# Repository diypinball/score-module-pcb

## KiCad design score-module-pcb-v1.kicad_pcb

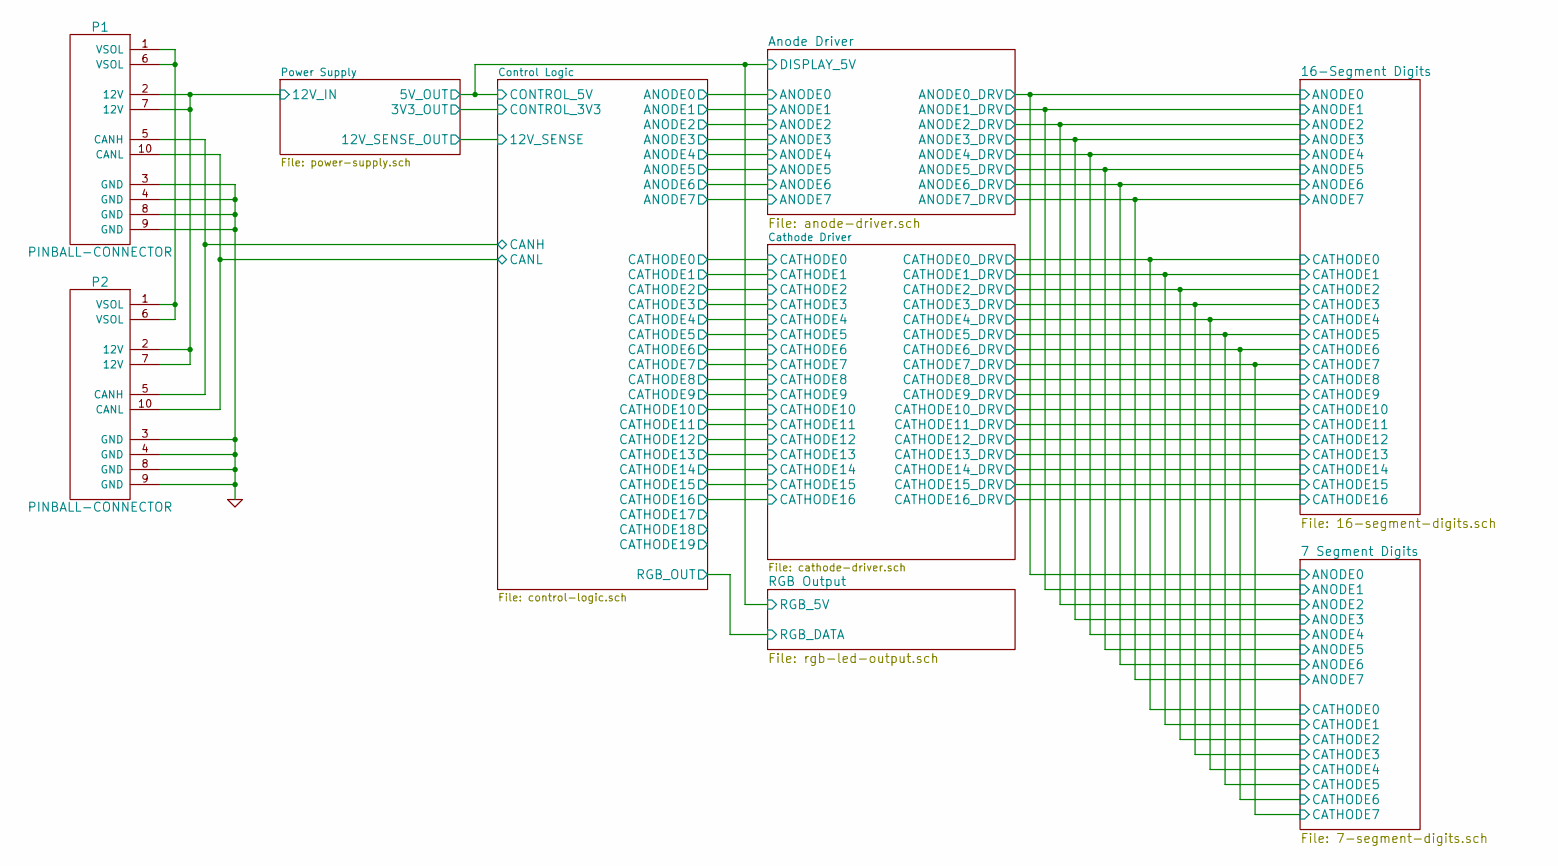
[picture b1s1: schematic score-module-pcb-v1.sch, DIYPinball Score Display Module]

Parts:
P1, P2: PINBALL-CONNECTOR; PINBALL-CONNECTOR-V

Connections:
/Control Logic/CANH: P1.5 (CANH), P2.5 (CANH); also elsewhere on the board
/Control Logic/CANL: P1.10 (CANL), P2.10 (CANL); also elsewhere on the board
/Power Supply/12V_IN: P1.2 (12V), P1.7 (12V), P2.2 (12V), P2.7 (12V); also elsewhere on the board
GND: P1.3 (GND), P1.4 (GND), P1.8 (GND), P1.9 (GND), P2.3 (GND), P2.4 (GND), P2.8 (GND), P2.9 (GND); also elsewhere on the board
unnamed: P1.1 (VSOL), P1.6 (VSOL), P2.1 (VSOL), P2.6 (VSOL)

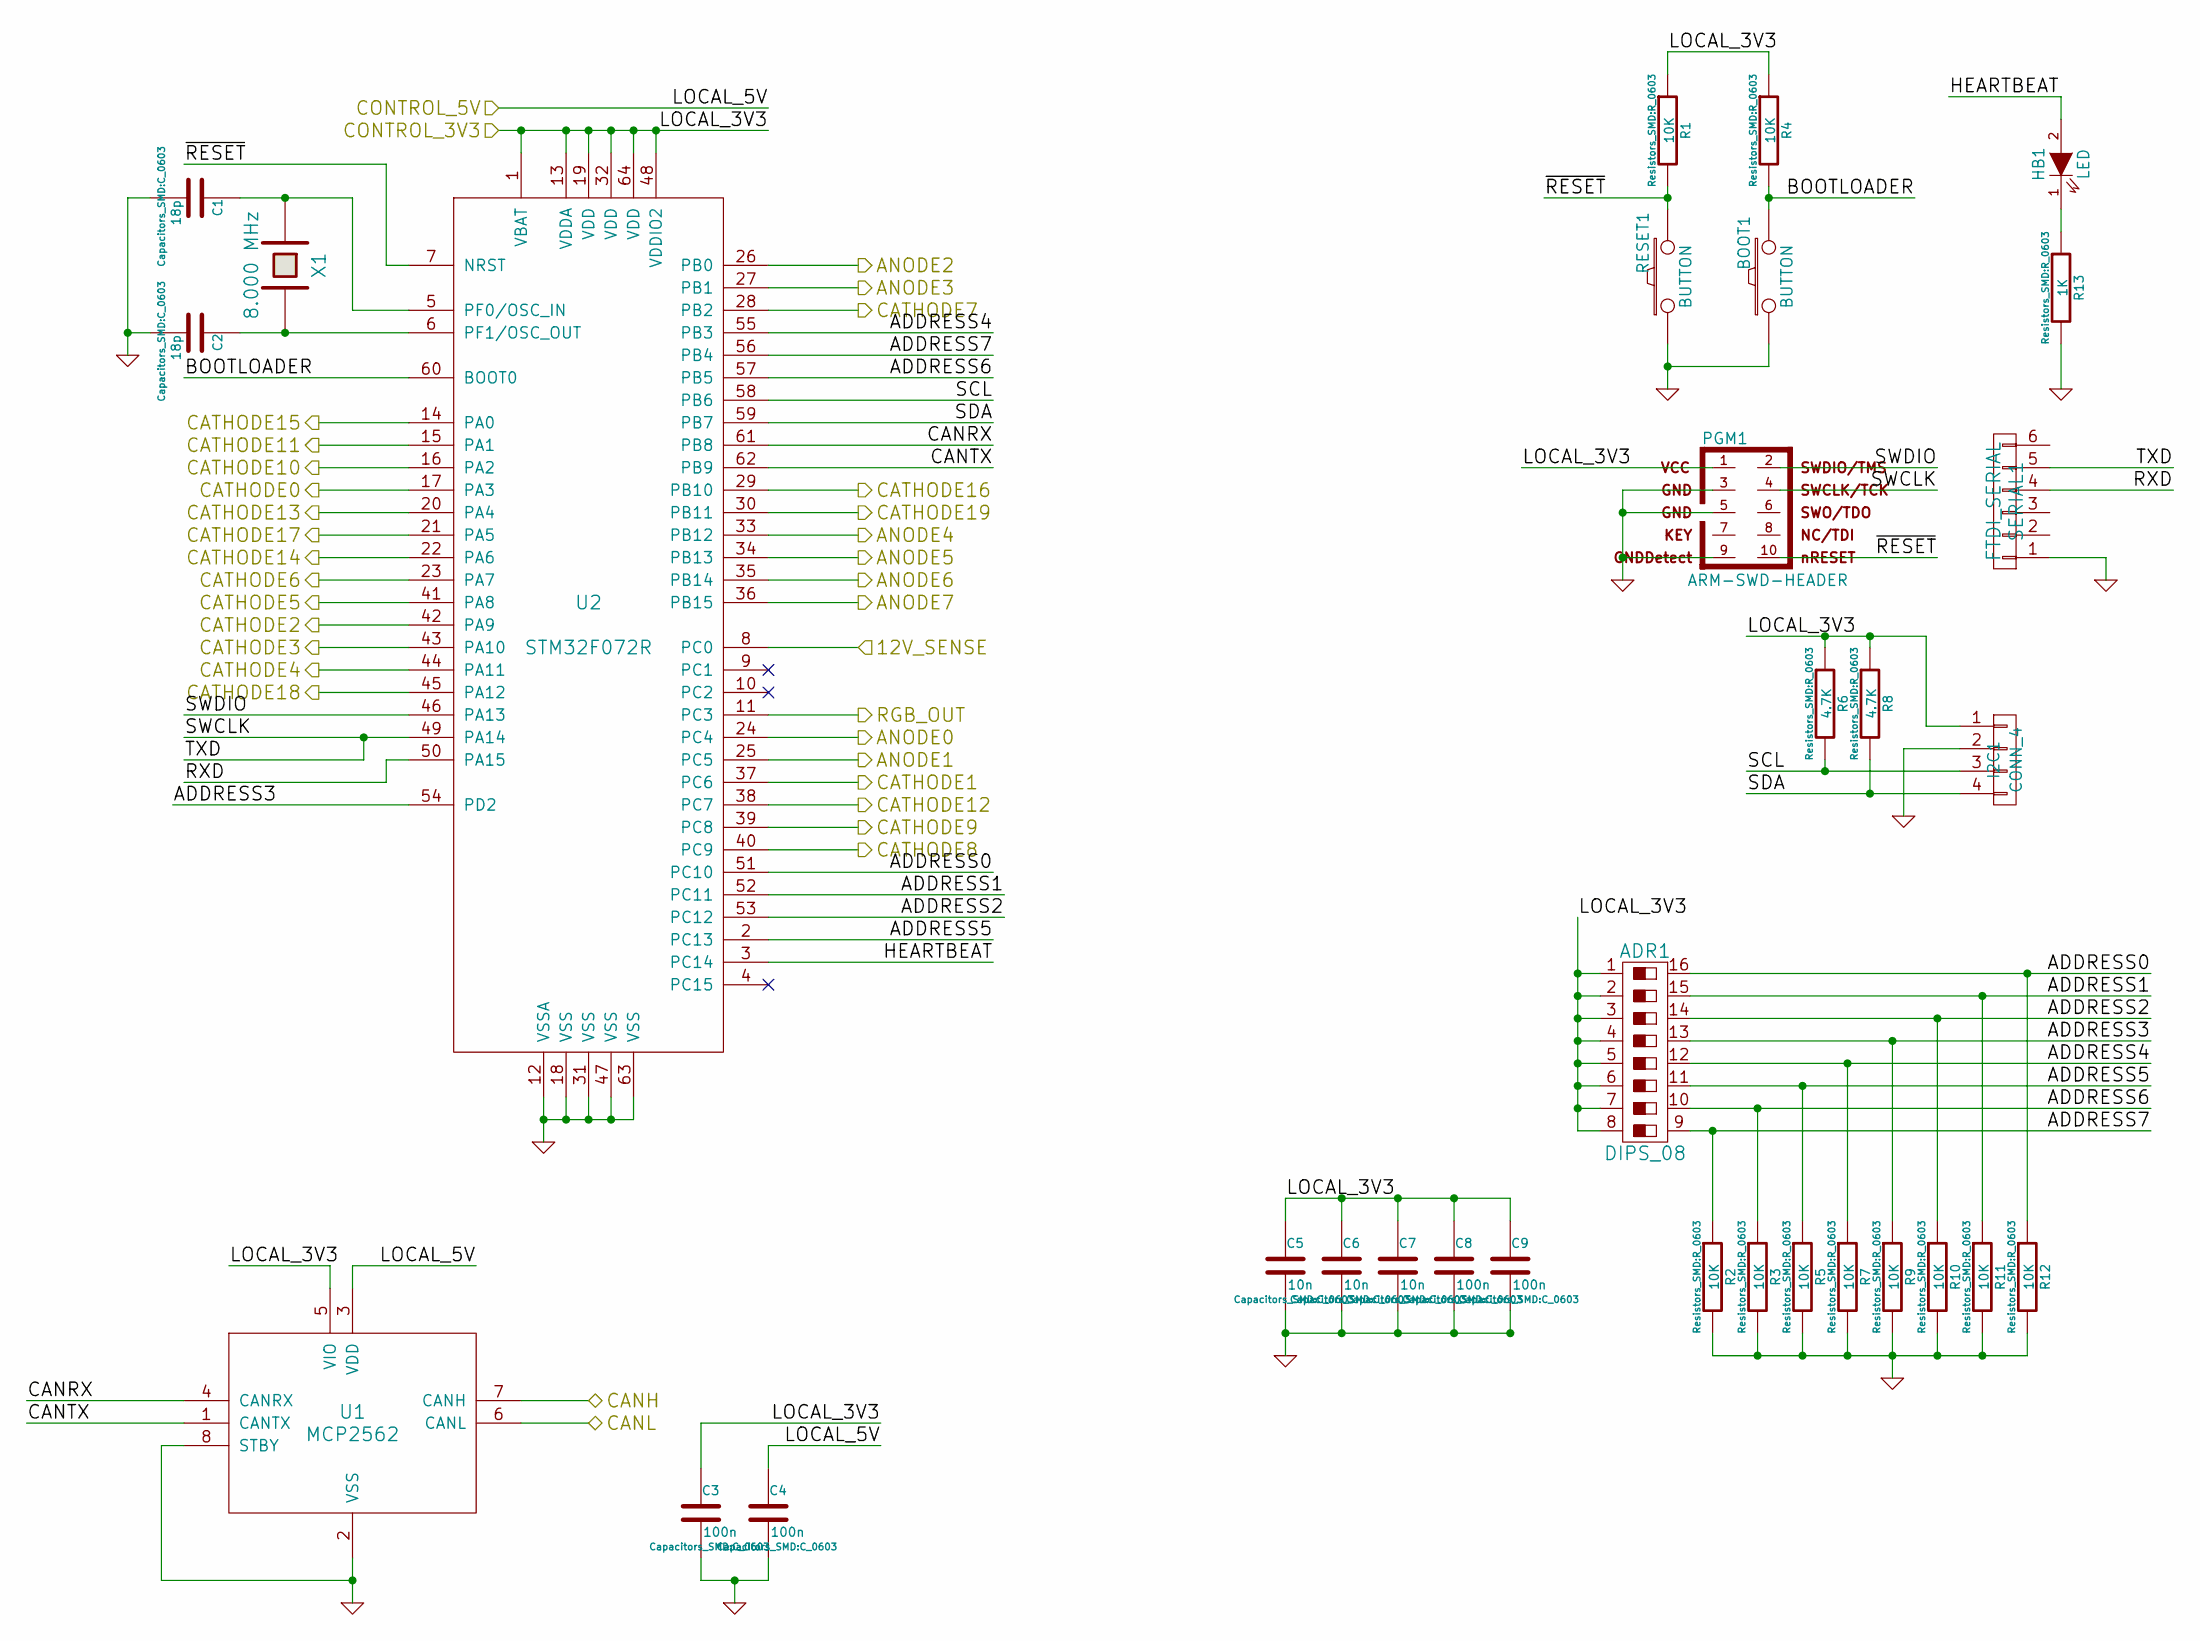
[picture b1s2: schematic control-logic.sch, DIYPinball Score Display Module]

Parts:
ADR1: DIPS_08; DIPSWITCH-SMT-08
BOOT1: BUTTON; SW_PUSH_SMALL
C1, C2: 18p; C_0603
C3, C4, C8, C9: 100n; C_0603
C5, C6, C7: 10n; C_0603
HB1: LED; LED-0603
I2C1: CONN_4; Socket_MOLEX-KK-RM2-54mm_Lock_4pin_straight
PGM1: ARM-SWD-HEADER; pin_array_5x2_50mil_smd
R1, R2, R3, R4, R5, R7, R9, R10, R11, R12: 10K; R_0603
R6, R8: 4.7K; R_0603
R13: 1K; R_0603
RESET1: BUTTON; SW_PUSH_SMALL
SERIAL1: FTDI_SERIAL; Socket_Strip_Straight_1x06
U1: MCP2562; SOIC-8_3.9x4.9mm_Pitch1.27mm
U2: STM32F072R; LQFP-64_10x10mm_Pitch0.5mm
X1: 8.000 MHz; Q_49U3HMS

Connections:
+3.3V: ADR1.1, ADR1.2, ADR1.3, ADR1.4, ADR1.5, ADR1.6, ADR1.7, ADR1.8, C3.1, C5.1, C6.1, C7.1, C8.1, C9.1, I2C1.1, PGM1.1, R1.1, R4.1, R6.1, R8.1, U1.5 (VIO), U2.1 (VBAT), U2.13 (VDDA), U2.19 (VDD), U2.32 (VDD), U2.48 (VDDIO2), U2.64 (VDD); also elsewhere on the board
+5V: C4.1, U1.3 (VDD); also elsewhere on the board
/Anode Driver/ANODE0: U2.24 (PC4); also elsewhere on the board
/Anode Driver/ANODE1: U2.25 (PC5); also elsewhere on the board
/Anode Driver/ANODE2: U2.26 (PB0); also elsewhere on the board
/Anode Driver/ANODE3: U2.27 (PB1); also elsewhere on the board
/Anode Driver/ANODE4: U2.33 (PB12); also elsewhere on the board
/Anode Driver/ANODE5: U2.34 (PB13); also elsewhere on the board
/Anode Driver/ANODE6: U2.35 (PB14); also elsewhere on the board
/Anode Driver/ANODE7: U2.36 (PB15); also elsewhere on the board
/Cathode Driver/CATHODE0: U2.17 (PA3); also elsewhere on the board
/Cathode Driver/CATHODE1: U2.37 (PC6); also elsewhere on the board
/Cathode Driver/CATHODE2: U2.42 (PA9); also elsewhere on the board
/Cathode Driver/CATHODE3: U2.43 (PA10); also elsewhere on the board
/Cathode Driver/CATHODE4: U2.44 (PA11); also elsewhere on the board
/Cathode Driver/CATHODE5: U2.41 (PA8); also elsewhere on the board
/Cathode Driver/CATHODE6: U2.23 (PA7); also elsewhere on the board
/Cathode Driver/CATHODE7: U2.28 (PB2); also elsewhere on the board
/Cathode Driver/CATHODE8: U2.40 (PC9); also elsewhere on the board
/Cathode Driver/CATHODE9: U2.39 (PC8); also elsewhere on the board
/Cathode Driver/CATHODE10: U2.16 (PA2); also elsewhere on the board
/Cathode Driver/CATHODE11: U2.15 (PA1); also elsewhere on the board
/Cathode Driver/CATHODE12: U2.38 (PC7); also elsewhere on the board
/Cathode Driver/CATHODE13: U2.20 (PA4); also elsewhere on the board
/Cathode Driver/CATHODE14: U2.22 (PA6); also elsewhere on the board
/Cathode Driver/CATHODE15: U2.14 (PA0); also elsewhere on the board
/Cathode Driver/CATHODE16: U2.29 (PB10); also elsewhere on the board
/Control Logic/12V_SENSE: U2.8 (PC0); also elsewhere on the board
/Control Logic/ADDRESS0: ADR1.16, R12.1, U2.51 (PC10)
/Control Logic/ADDRESS1: ADR1.15, R11.1, U2.52 (PC11)
/Control Logic/ADDRESS2: ADR1.14, R10.1, U2.53 (PC12)
/Control Logic/ADDRESS3: ADR1.13, R9.1, U2.54 (PD2)
/Control Logic/ADDRESS4: ADR1.12, R7.1, U2.55 (PB3)
/Control Logic/ADDRESS5: ADR1.11, R5.1, U2.2 (PC13)
/Control Logic/ADDRESS6: ADR1.10, R3.1, U2.57 (PB5)
/Control Logic/ADDRESS7: ADR1.9, R2.1, U2.56 (PB4)
/Control Logic/BOOTLOADER: BOOT1.2, R4.2, U2.60 (BOOT0)
/Control Logic/CANH: U1.7 (CANH); also elsewhere on the board
/Control Logic/CANL: U1.6 (CANL); also elsewhere on the board
/Control Logic/CANRX: U1.4 (CANRX), U2.61 (PB8)
/Control Logic/CANTX: U1.1 (CANTX), U2.62 (PB9)
/Control Logic/HEARTBEAT: HB1.2 (A), U2.3 (PC14)
/Control Logic/RXD: SERIAL1.4, U2.50 (PA15)
/Control Logic/SCL: I2C1.3, R6.2, U2.58 (PB6)
/Control Logic/SDA: I2C1.4, R8.2, U2.59 (PB7)
/Control Logic/SWCLK: PGM1.4, SERIAL1.5, U2.49 (PA14)
/Control Logic/SWDIO: PGM1.2, U2.46 (PA13)
/Control Logic/~RESET: PGM1.10, R1.2, RESET1.2, U2.7 (NRST)
/RGB Output/RGB_DATA: U2.11 (PC3); also elsewhere on the board
GND: BOOT1.1, C1.2, C2.2, C3.2, C4.2, C5.2, C6.2, C7.2, C8.2, C9.2, I2C1.2, PGM1.3, PGM1.5, PGM1.9, R2.2, R3.2, R5.2, R7.2, R9.2, R10.2, R11.2, R12.2, R13.2, RESET1.1, SERIAL1.1, U1.2 (VSS), U1.8 (STBY), U2.12 (VSSA), U2.18 (VSS), U2.31 (VSS), U2.47 (VSS), U2.63 (VSS); also elsewhere on the board
unnamed: C1.1, U2.5 (PF0/OSC_IN), X1.1
unnamed: C2.1, U2.6 (PF1/OSC_OUT), X1.2
unnamed: HB1.1 (K), R13.1

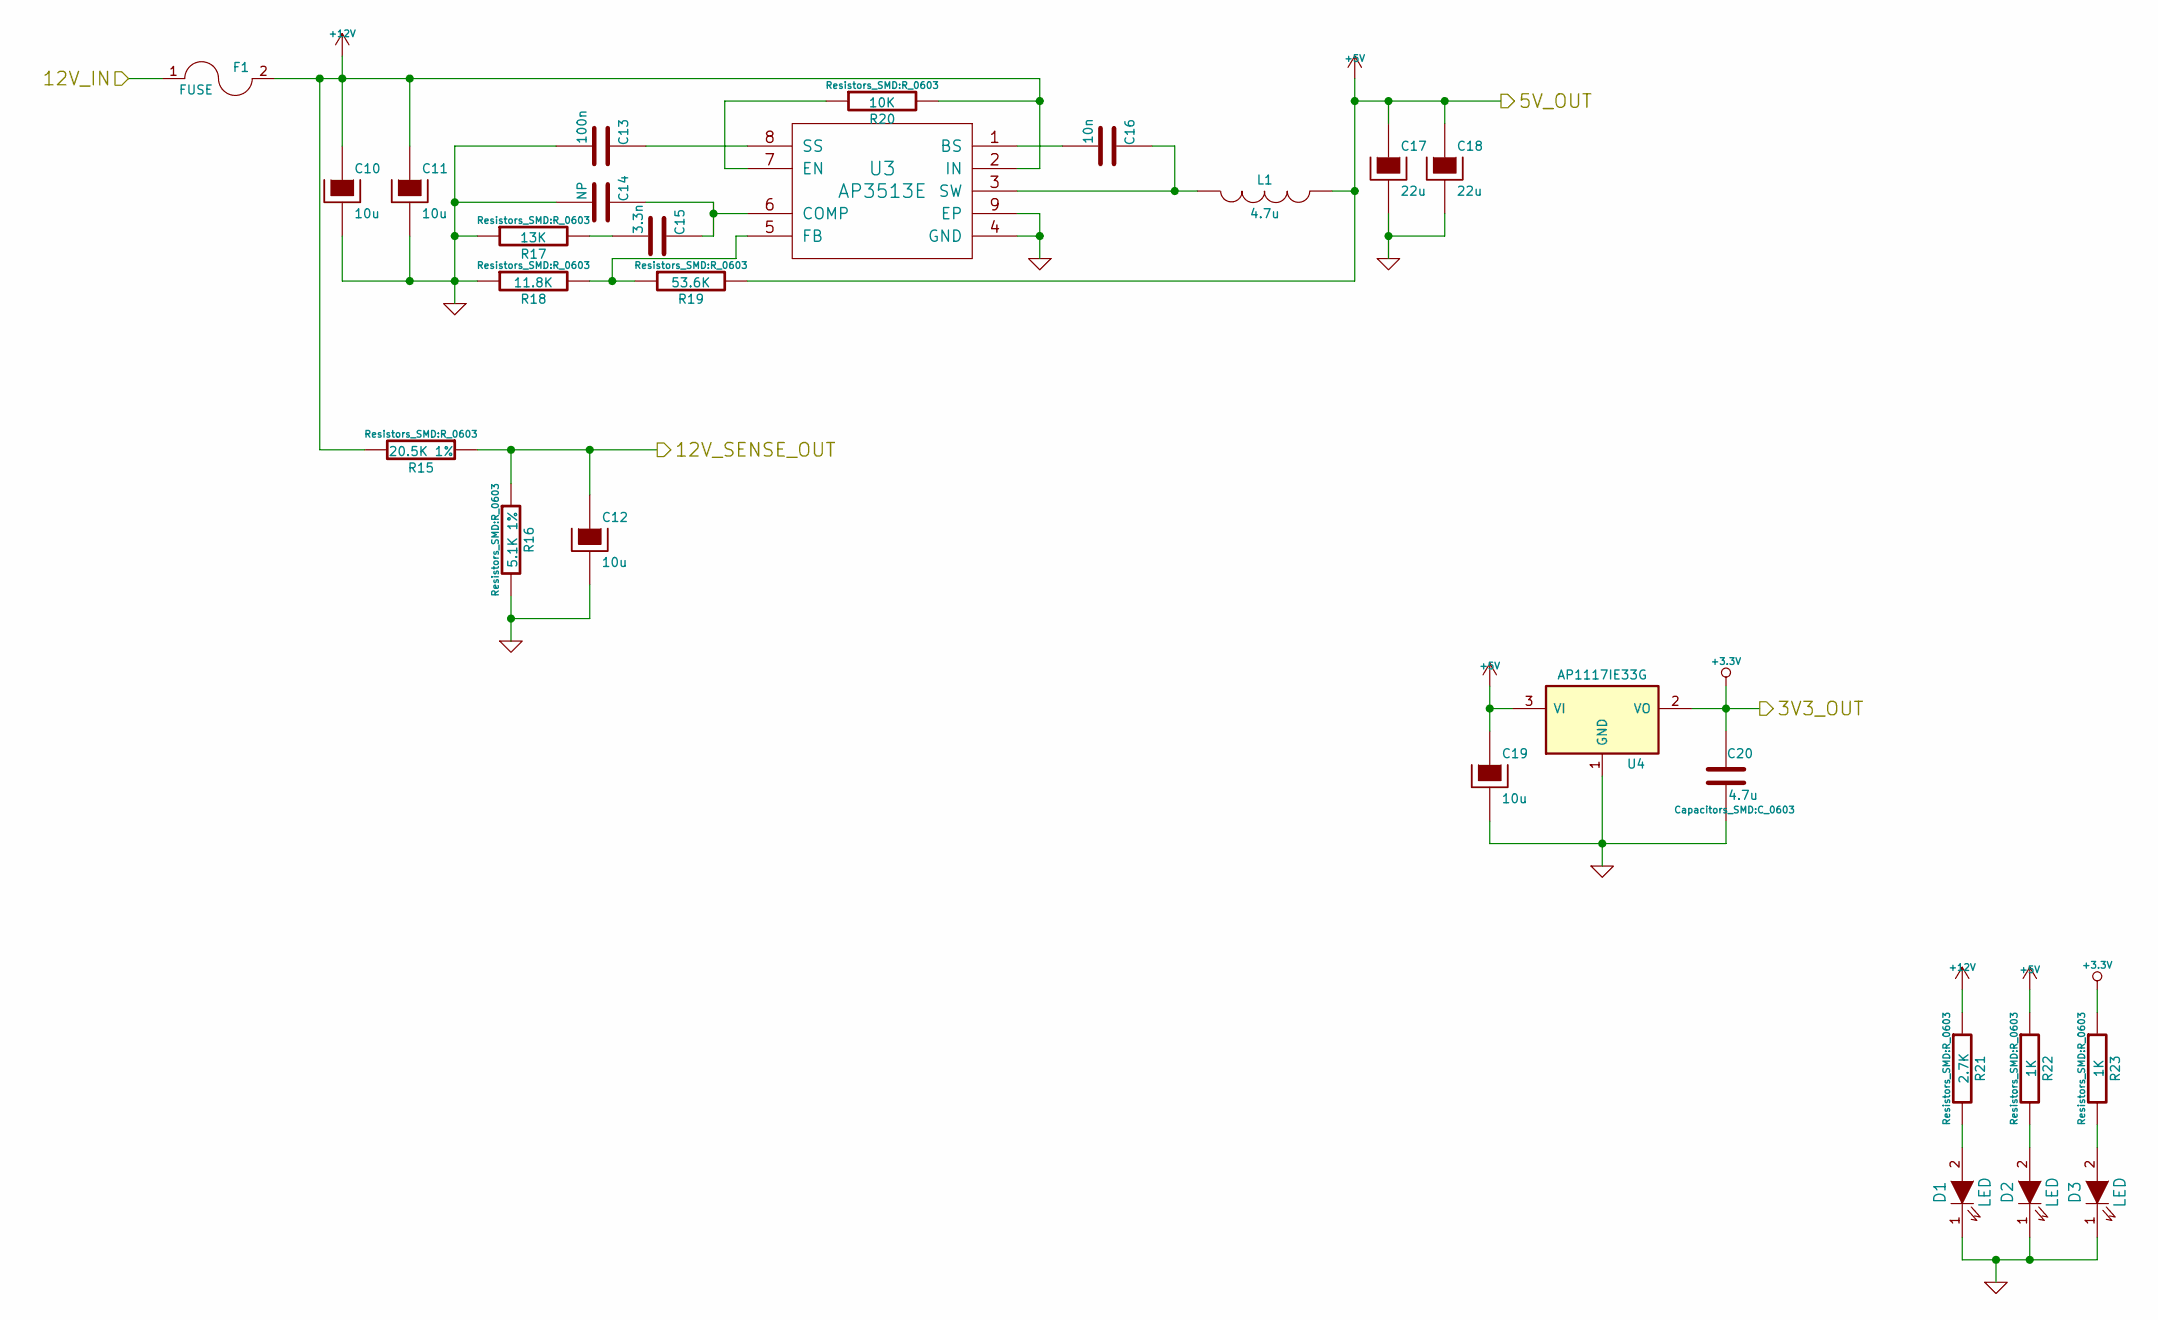
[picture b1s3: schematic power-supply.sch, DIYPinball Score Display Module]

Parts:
C10, C11: 10u; c_elec_5x5.8
C12, C19: 10u; C_0805
C13: 100n; C_0603
C14: NP; C_0603
C15: 3.3n; C_0603
C16: 10n; C_0603
C17, C18: 22u; c_elec_5x5.8
C20: 4.7u; C_0603
D1, D2, D3: LED; LED-0603
F1: FUSE; FC203-20MM
L1: 4.7u; SELF-WE-PD3S
R15: 20.5K 1%; R_0603
R16: 5.1K 1%; R_0603
R17: 13K; R_0603
R18: 11.8K; R_0603
R19: 53.6K; R_0603
R20: 10K; R_0603
R21: 2.7K; R_0603
R22, R23: 1K; R_0603
U3: AP3513E; SOIC-8-1EP_3.9x4.9mm_Pitch1.27mm
U4: AP1117IE33G; SOT-223

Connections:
+3.3V: C20.1, R23.1, U4.2 (VO); also elsewhere on the board
+5V: C17.1, C18.1, C19.1, L1.2, R19.2, R22.1, U4.3 (VI); also elsewhere on the board
+12V: C10.1, C11.1, F1.2, R15.2, R20.2, R21.1, U3.2 (IN)
/Control Logic/12V_SENSE: C12.1, R15.1, R16.1; also elsewhere on the board
/Power Supply/12V_IN: F1.1; also elsewhere on the board
GND: C10.2, C11.2, C12.2, C13.2, C14.2, C17.2, C18.2, C19.2, C20.2, D1.1 (K), D2.1 (K), D3.1 (K), R16.2, R17.1, R18.1, U3.4 (GND), U3.9 (EP), U4.1 (GND); also elsewhere on the board
unnamed: C13.1, U3.8 (SS)
unnamed: C14.1, C15.1, U3.6 (COMP)
unnamed: C15.2, R17.2
unnamed: C16.1, L1.1, U3.3 (SW)
unnamed: C16.2, U3.1 (BS)
unnamed: D1.2 (A), R21.2
unnamed: D2.2 (A), R22.2
unnamed: D3.2 (A), R23.2
unnamed: R18.2, R19.1, U3.5 (FB)
unnamed: R20.1, U3.7 (EN)

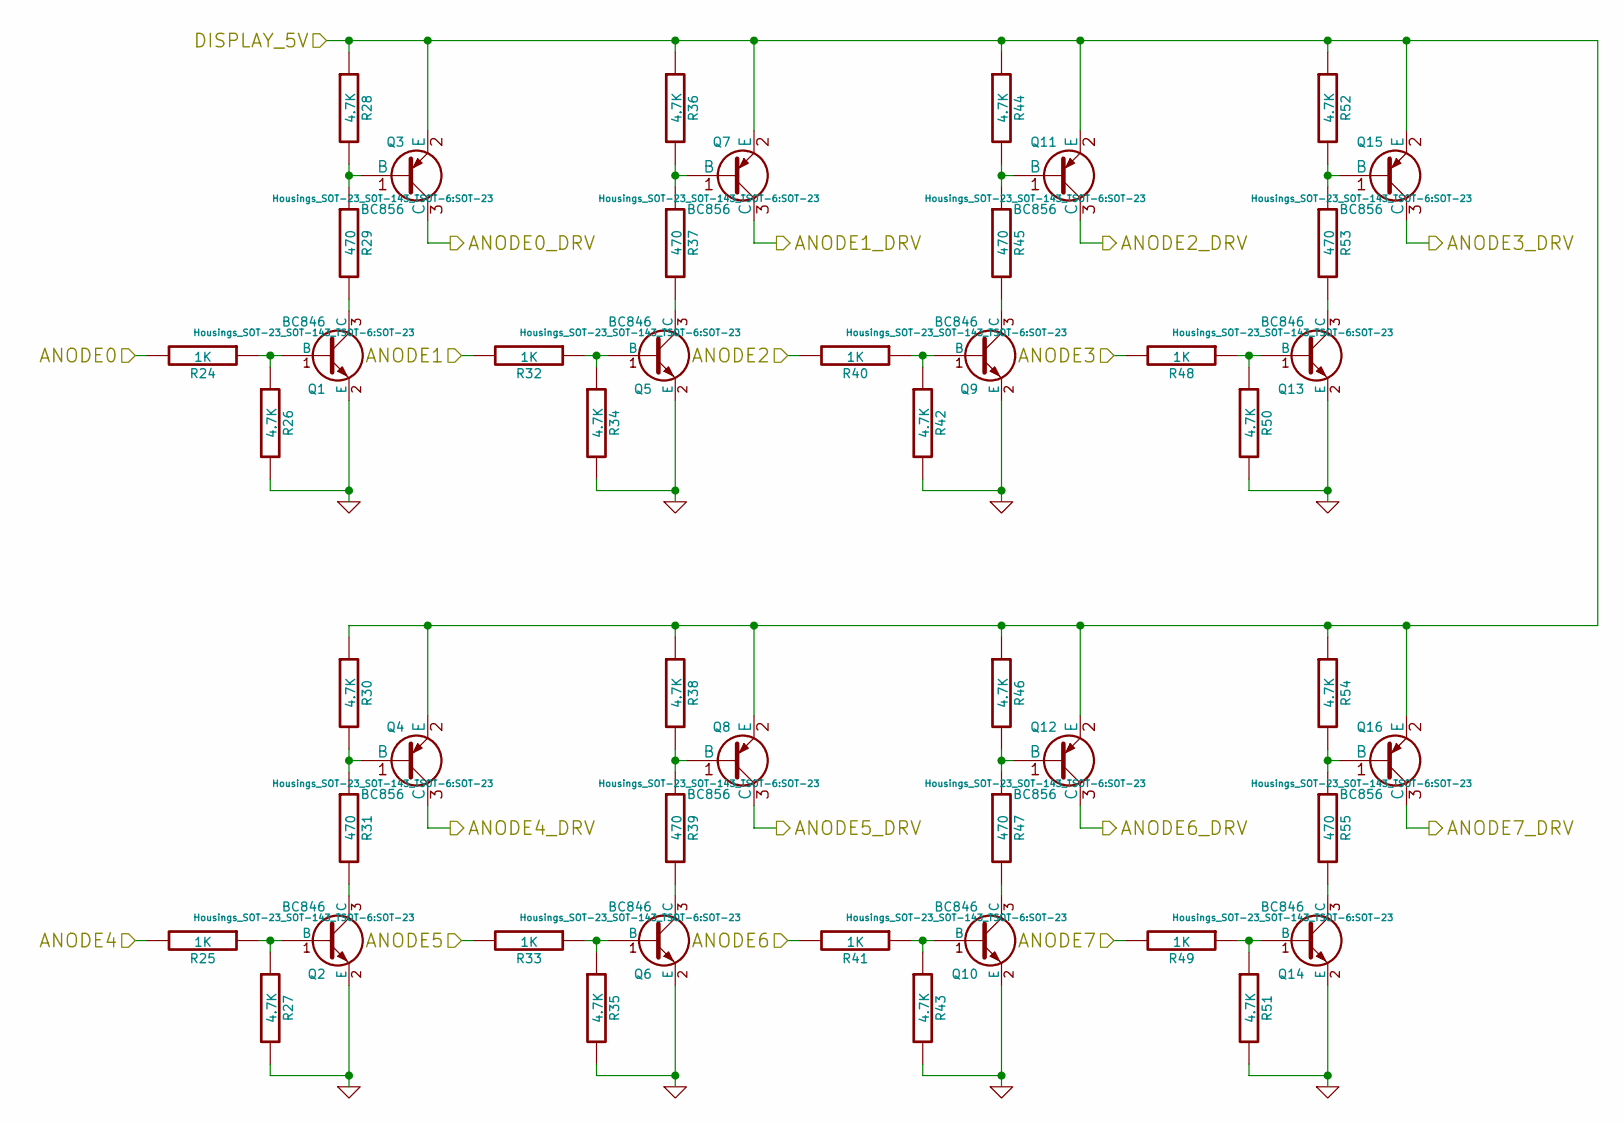
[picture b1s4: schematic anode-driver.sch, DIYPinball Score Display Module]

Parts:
Q1, Q2, Q5, Q6, Q9, Q10, Q13, Q14: BC846; SOT-23
Q3, Q4, Q7, Q8, Q11, Q12, Q15, Q16: BC856; SOT-23
R24, R25, R32, R33, R40, R41, R48, R49: 1K; R_0603
R26, R27, R28, R30, R34, R35, R36, R38, R42, R43, R44, R46, R50, R51, R52, R54: 4.7K; R_0603
R29, R31, R37, R39, R45, R47, R53, R55: 470; R_0603

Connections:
+5V: Q3.2 (E), Q4.2 (E), Q7.2 (E), Q8.2 (E), Q11.2 (E), Q12.2 (E), Q15.2 (E), Q16.2 (E), R28.1, R30.1, R36.1, R38.1, R44.1, R46.1, R52.1, R54.1; also elsewhere on the board
/16-Segment Digits/ANODE0: Q3.3 (C); also elsewhere on the board
/16-Segment Digits/ANODE1: Q7.3 (C); also elsewhere on the board
/16-Segment Digits/ANODE2: Q11.3 (C); also elsewhere on the board
/16-Segment Digits/ANODE3: Q15.3 (C); also elsewhere on the board
/16-Segment Digits/ANODE4: Q4.3 (C); also elsewhere on the board
/16-Segment Digits/ANODE5: Q8.3 (C); also elsewhere on the board
/16-Segment Digits/ANODE6: Q12.3 (C); also elsewhere on the board
/16-Segment Digits/ANODE7: Q16.3 (C); also elsewhere on the board
/Anode Driver/ANODE0: R24.2; also elsewhere on the board
/Anode Driver/ANODE1: R32.2; also elsewhere on the board
/Anode Driver/ANODE2: R40.2; also elsewhere on the board
/Anode Driver/ANODE3: R48.2; also elsewhere on the board
/Anode Driver/ANODE4: R25.2; also elsewhere on the board
/Anode Driver/ANODE5: R33.2; also elsewhere on the board
/Anode Driver/ANODE6: R41.2; also elsewhere on the board
/Anode Driver/ANODE7: R49.2; also elsewhere on the board
GND: Q1.2 (E), Q2.2 (E), Q5.2 (E), Q6.2 (E), Q9.2 (E), Q10.2 (E), Q13.2 (E), Q14.2 (E), R26.2, R27.2, R34.2, R35.2, R42.2, R43.2, R50.2, R51.2; also elsewhere on the board
unnamed: Q1.1 (B), R24.1, R26.1
unnamed: Q1.3 (C), R29.2
unnamed: Q2.1 (B), R25.1, R27.1
unnamed: Q2.3 (C), R31.2
unnamed: Q3.1 (B), R28.2, R29.1
unnamed: Q4.1 (B), R30.2, R31.1
unnamed: Q5.1 (B), R32.1, R34.1
unnamed: Q5.3 (C), R37.2
unnamed: Q6.1 (B), R33.1, R35.1
unnamed: Q6.3 (C), R39.2
unnamed: Q7.1 (B), R36.2, R37.1
unnamed: Q8.1 (B), R38.2, R39.1
unnamed: Q9.1 (B), R40.1, R42.1
unnamed: Q9.3 (C), R45.2
unnamed: Q10.1 (B), R41.1, R43.1
unnamed: Q10.3 (C), R47.2
unnamed: Q11.1 (B), R44.2, R45.1
unnamed: Q12.1 (B), R46.2, R47.1
unnamed: Q13.1 (B), R48.1, R50.1
unnamed: Q13.3 (C), R53.2
unnamed: Q14.1 (B), R49.1, R51.1
unnamed: Q14.3 (C), R55.2
unnamed: Q15.1 (B), R52.2, R53.1
unnamed: Q16.1 (B), R54.2, R55.1

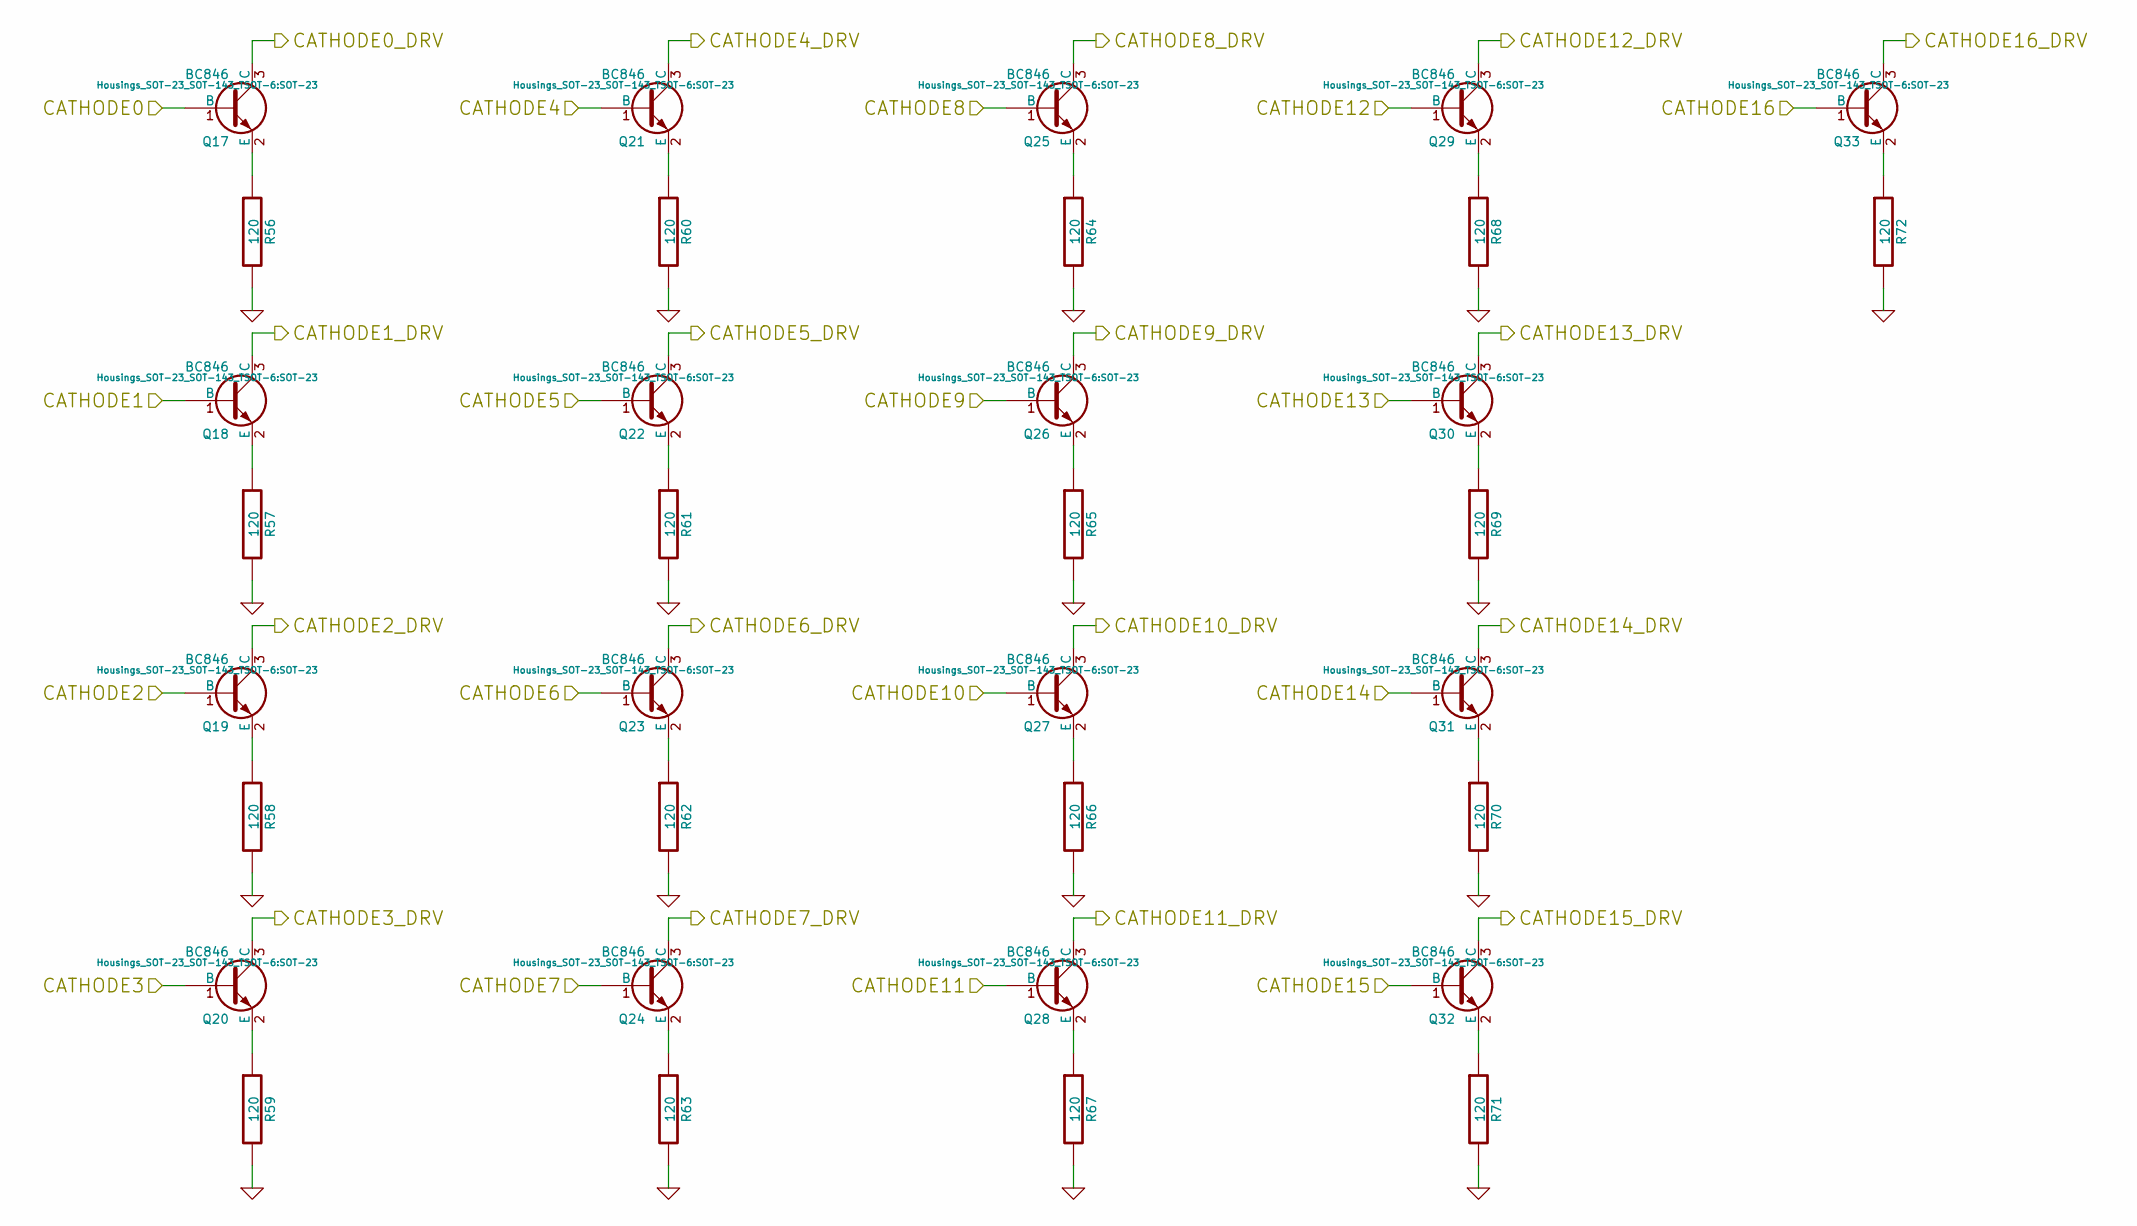
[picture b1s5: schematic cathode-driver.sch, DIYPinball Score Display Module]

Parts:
Q17, Q18, Q19, Q20, Q21, Q22, Q23, Q24, Q25, Q26, Q27, Q28, Q29, Q30, Q31, Q32, Q33: BC846; SOT-23
R56, R57, R58, R59, R60, R61, R62, R63, R64, R65, R66, R67, R68, R69, R70, R71, R72: 120; R_0603

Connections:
/16-Segment Digits/CATHODE0: Q17.3 (C); also elsewhere on the board
/16-Segment Digits/CATHODE1: Q18.3 (C); also elsewhere on the board
/16-Segment Digits/CATHODE2: Q19.3 (C); also elsewhere on the board
/16-Segment Digits/CATHODE3: Q20.3 (C); also elsewhere on the board
/16-Segment Digits/CATHODE4: Q21.3 (C); also elsewhere on the board
/16-Segment Digits/CATHODE5: Q22.3 (C); also elsewhere on the board
/16-Segment Digits/CATHODE6: Q23.3 (C); also elsewhere on the board
/16-Segment Digits/CATHODE7: Q24.3 (C); also elsewhere on the board
/16-Segment Digits/CATHODE8: Q25.3 (C); also elsewhere on the board
/16-Segment Digits/CATHODE9: Q26.3 (C); also elsewhere on the board
/16-Segment Digits/CATHODE10: Q27.3 (C); also elsewhere on the board
/16-Segment Digits/CATHODE11: Q28.3 (C); also elsewhere on the board
/16-Segment Digits/CATHODE12: Q29.3 (C); also elsewhere on the board
/16-Segment Digits/CATHODE13: Q30.3 (C); also elsewhere on the board
/16-Segment Digits/CATHODE14: Q31.3 (C); also elsewhere on the board
/16-Segment Digits/CATHODE15: Q32.3 (C); also elsewhere on the board
/16-Segment Digits/CATHODE16: Q33.3 (C); also elsewhere on the board
/Cathode Driver/CATHODE0: Q17.1 (B); also elsewhere on the board
/Cathode Driver/CATHODE1: Q18.1 (B); also elsewhere on the board
/Cathode Driver/CATHODE2: Q19.1 (B); also elsewhere on the board
/Cathode Driver/CATHODE3: Q20.1 (B); also elsewhere on the board
/Cathode Driver/CATHODE4: Q21.1 (B); also elsewhere on the board
/Cathode Driver/CATHODE5: Q22.1 (B); also elsewhere on the board
/Cathode Driver/CATHODE6: Q23.1 (B); also elsewhere on the board
/Cathode Driver/CATHODE7: Q24.1 (B); also elsewhere on the board
/Cathode Driver/CATHODE8: Q25.1 (B); also elsewhere on the board
/Cathode Driver/CATHODE9: Q26.1 (B); also elsewhere on the board
/Cathode Driver/CATHODE10: Q27.1 (B); also elsewhere on the board
/Cathode Driver/CATHODE11: Q28.1 (B); also elsewhere on the board
/Cathode Driver/CATHODE12: Q29.1 (B); also elsewhere on the board
/Cathode Driver/CATHODE13: Q30.1 (B); also elsewhere on the board
/Cathode Driver/CATHODE14: Q31.1 (B); also elsewhere on the board
/Cathode Driver/CATHODE15: Q32.1 (B); also elsewhere on the board
/Cathode Driver/CATHODE16: Q33.1 (B); also elsewhere on the board
GND: R56.2, R57.2, R58.2, R59.2, R60.2, R61.2, R62.2, R63.2, R64.2, R65.2, R66.2, R67.2, R68.2, R69.2, R70.2, R71.2, R72.2; also elsewhere on the board
unnamed: Q17.2 (E), R56.1
unnamed: Q18.2 (E), R57.1
unnamed: Q19.2 (E), R58.1
unnamed: Q20.2 (E), R59.1
unnamed: Q21.2 (E), R60.1
unnamed: Q22.2 (E), R61.1
unnamed: Q23.2 (E), R62.1
unnamed: Q24.2 (E), R63.1
unnamed: Q25.2 (E), R64.1
unnamed: Q26.2 (E), R65.1
unnamed: Q27.2 (E), R66.1
unnamed: Q28.2 (E), R67.1
unnamed: Q29.2 (E), R68.1
unnamed: Q30.2 (E), R69.1
unnamed: Q31.2 (E), R70.1
unnamed: Q32.2 (E), R71.1
unnamed: Q33.2 (E), R72.1
